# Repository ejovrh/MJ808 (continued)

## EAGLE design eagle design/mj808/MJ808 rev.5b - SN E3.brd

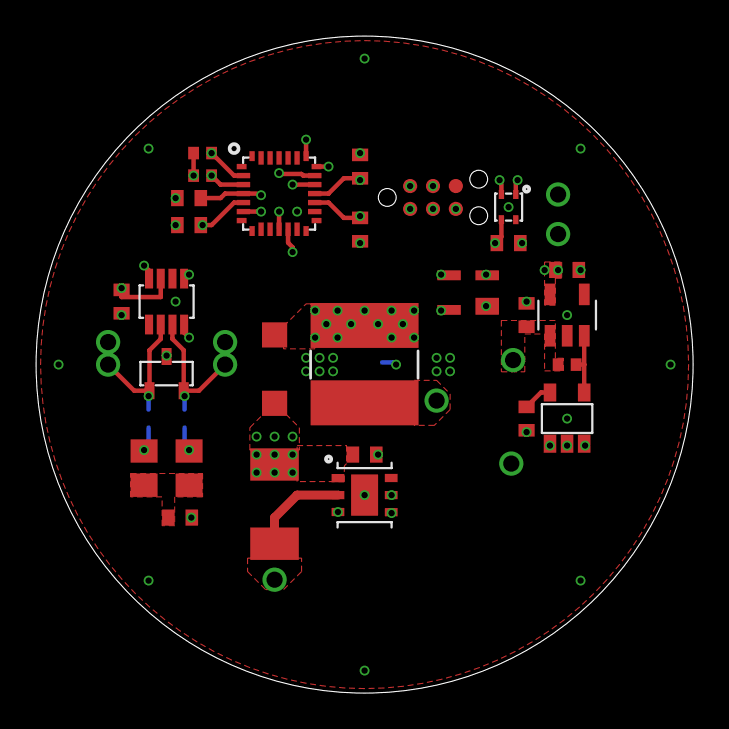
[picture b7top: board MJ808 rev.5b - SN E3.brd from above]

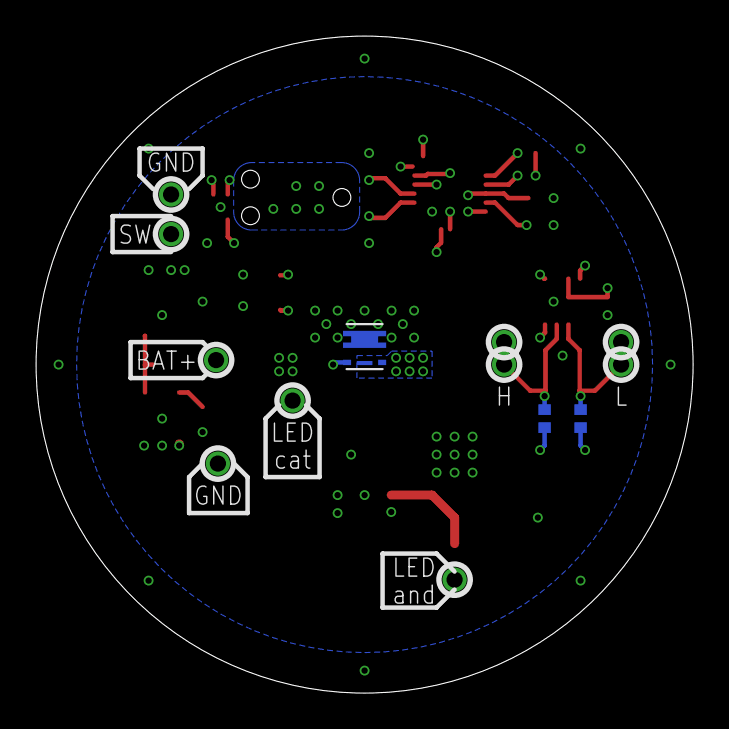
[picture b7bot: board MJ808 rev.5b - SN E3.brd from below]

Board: 4 copper layers, 36.5 x 36.5 mm, 41 parts (13 on the bottom side), 25 nets.

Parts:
C201, C202, C207, C304, C506: 1uF / 10V; C0402
C301, C305, C307, C405, C705: 0.1uF / 10V; C0402
C401: 47nF / 10V; C0402
D501: PMEG2010ER,115; SOD123
IC201: R3119N058A; SOT23-5
IC202: LDK320AM33R; SOT-23-5L
IC302: STM32F042G6U6; UFQFPN-28
IC401: TCAN334; SOT23-8
IC402: SZNUP2105LT1G; SOT-23-3
IC506: MAX16820; TDFN-6-EP
IC507: SQA470EEJ-T1_GE3; SC-70-6
IC602: MAX6816EUS+T; 4SOT143
IC701: SHT40-AD1F-R2; SMD
L501: VLS6045EX-150M-CA - 15uH; SRN6045
R201: 100k / 0.1W; R0402
R301, R302: 1k; R0402
R401, R402: 60R, 0.5W; R0805
R403, R404: 0; R0402
R504: 0.18R; R2010
SWD1: TC2030-NL
TP1: LiIon + Terminal; TH-0.9
TP2: LiIon - Terminal; TH-0.9
TP3, TP601, TP602: LED anode; TH-0.9
TP4: LED cathode; TH-0.9
TP5, TP7: CAN high; TH-0.9
TP6, TP8: CAN low; TH-0.9

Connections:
3V3: C207.2, C301.2, C304.2, C305.2, C405.1, C705.1, IC202.OUT, IC302.5_VDDA, IC302.17_VDD, IC302.18_VDDIO2, IC401.P$3, IC602.4_VCC, IC701.VDD, R301.2, R302.2, SWD1.1_TVCC
!STBY!: IC302.11_PA5, IC401.P$8
BAT+: C202.1, C506.1, D501.C, IC201.1_VDD, IC202.IN, IC506.IN, R201.1, R504.2, TP1.P$1
CAN_H: IC401.P$7, IC402.2, R403.2, TP5.P$1, TP7.P$1
CAN_INFRA:H: R402.2, R403.1
CAN_INFRA:L: R401.1, R404.1
CAN_INFRA:SPLIT: C401.1, R401.2, R402.1
CAN_L: IC401.P$6, IC402.1, R404.2, TP6.P$1, TP8.P$1
CAN_RX: IC302.19_PA9-[PA11], IC401.P$4
CAN_TX: IC302.20_PA10-[PA12], IC401.P$1
DIM_FRONT: IC302.12_PA6, IC506.DIM
FRONT_LED_DRIVER:DIM_FRONT_DRAIN: D501.A, IC507.1D, IC507.2D, IC507.5D, IC507.6D, IC507.D, L501.1
FRONT_LED_DRIVER:DIM_FRONT_GATE: IC506.DRV, IC507.3G
GND: C201.2, C202.2, C207.1, C301.1, C304.1, C305.1, C307.1, C401.2, C405.2, C506.2, C705.2, IC201.2_GND, IC201.3_GND, IC202.GND, IC302.16_VSS, IC401.P$2, IC402.3, IC506.GND, IC506.GND1, IC507.4S, IC507.S, IC602.1_GND, IC701.VSS, SWD1.5_GND, TP2.P$1, TP602.P$1
I2C_SCL: IC302.3_PF1, IC701.SCL, R302.1
I2C_SDA: IC302.2_PF0, IC701.SDA, R301.1
LED_AN: IC506.CSN, R504.1, TP3.P$1
LED_CA: L501.2, TP4.P$1
POWER_3V3:CD: C201.1, IC201.5_CD
POWER_3V3:EN: IC201.4_DOUT, IC202.EN, R201.2
PUSHBUTTON:SWITCH_IN: IC602.2_IN, TP601.P$1
SWITCH: IC302.6_PA0, IC602.3_OUT
SYS_NRST: C307.2, IC302.4_NRST, SWD1.3_T_NRST
SYS_SWCLK: IC302.22_PA14, SWD1.4_T_SWCLK
SYS_SWDIO: IC302.21_PA13, SWD1.2_T_SWDIO

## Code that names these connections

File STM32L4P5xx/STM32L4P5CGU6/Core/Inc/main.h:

/* USER CODE BEGIN Header */
/**
  ******************************************************************************
  * @file           : main.h
  * @brief          : Header for main.c file.
  *                   This file contains the common defines of the application.
  ******************************************************************************
  * @attention
  *
  * Copyright (c) 2025 STMicroelectronics.
  * All rights reserved.
  *
  * This software is licensed under terms that can be found in the LICENSE file
  * in the root directory of this software component.
  * If no LICENSE file comes with this software, it is provided AS-IS.
  *
  ******************************************************************************
  */
/* USER CODE END Header */

/* Define to prevent recursive inclusion -------------------------------------*/
#ifndef __MAIN_H
#define __MAIN_H

#ifdef __cplusplus
extern "C" {
#endif

/* Includes ------------------------------------------------------------------*/
#include "stm32l4xx_hal.h"

/* Private includes ----------------------------------------------------------*/
/* USER CODE BEGIN Includes */

/* USER CODE END Includes */

/* Exported types ------------------------------------------------------------*/
/* USER CODE BEGIN ET */

/* USER CODE END ET */

/* Exported constants --------------------------------------------------------*/
/* USER CODE BEGIN EC */

/* USER CODE END EC */

/* Exported macro ------------------------------------------------------------*/
/* USER CODE BEGIN EM */

/* USER CODE END EM */

/* Exported functions prototypes ---------------------------------------------*/
void Error_Handler(void);

/* USER CODE BEGIN EFP */

/* USER CODE END EFP */

/* Private defines -----------------------------------------------------------*/
#define TIMER_PRESCALER 799
#define TIMER2_PERIOD 0xFFFFFFFF
#define TIMER1_PERIOD 1249
#define TIMER1_PRESCALER 799
#define TIMER2_CH1_IC_FILTER 0xF
#define TIMER2_CH3_IC_FILTER 0xF
#define RN4678_SWButton_Pin GPIO_PIN_13
#define RN4678_SWButton_GPIO_Port GPIOC
#define RN4678_TransStat_Pin GPIO_PIN_14
#define RN4678_TransStat_GPIO_Port GPIOC
#define RN4678_ConnStat_Pin GPIO_PIN_15
#define RN4678_ConnStat_GPIO_Port GPIOC
#define HSE_IN_Pin GPIO_PIN_0
#define HSE_IN_GPIO_Port GPIOH
#define HSE_OUT_Pin GPIO_PIN_1
#define HSE_OUT_GPIO_Port GPIOH
#define ZeroCross_Pin GPIO_PIN_0
#define ZeroCross_GPIO_Port GPIOA
#define SDMMC_CMD_Pin GPIO_PIN_1
#define SDMMC_CMD_GPIO_Port GPIOA
#define DynamoCurrent_Pin GPIO_PIN_2
#define DynamoCurrent_GPIO_Port GPIOA
#define TCAN334_Standby_Pin GPIO_PIN_3
#define TCAN334_Standby_GPIO_Port GPIOA
#define AdjustableLoadDAC_Pin GPIO_PIN_4
#define AdjustableLoadDAC_GPIO_Port GPIOA
#define ADXL_INT1_Pin GPIO_PIN_5
#define ADXL_INT1_GPIO_Port GPIOA
#define QSPI_IO3_Pin GPIO_PIN_6
#define QSPI_IO3_GPIO_Port GPIOA
#define QSPI_IO2_Pin GPIO_PIN_7
#define QSPI_IO2_GPIO_Port GPIOA
#define QSPI_IO1_Pin GPIO_PIN_0
#define QSPI_IO1_GPIO_Port GPIOB
#define QSPI_IO0_Pin GPIO_PIN_1
#define QSPI_IO0_GPIO_Port GPIOB
#define RN4678_Reset_Pin GPIO_PIN_2
#define RN4678_Reset_GPIO_Port GPIOB
#define QSPI_SCK_Pin GPIO_PIN_10
#define QSPI_SCK_GPIO_Port GPIOB
#define QSPI_CS_Pin GPIO_PIN_11
#define QSPI_CS_GPIO_Port GPIOB
#define SDMMC_CLK_Pin GPIO_PIN_12
#define SDMMC_CLK_GPIO_Port GPIOB
#define SDMMC_CardDetect_Pin GPIO_PIN_13
#define SDMMC_CardDetect_GPIO_Port GPIOB
#define SDMMC_Data0_Pin GPIO_PIN_14
#define SDMMC_Data0_GPIO_Port GPIOB
#define SDMMC_Data1_Pin GPIO_PIN_15
#define SDMMC_Data1_GPIO_Port GPIOB
#define ApplicationLoadGate_Pin GPIO_PIN_8
#define ApplicationLoadGate_GPIO_Port GPIOA
#define RN4678_TX_Pin GPIO_PIN_9
#define RN4678_TX_GPIO_Port GPIOA
#define RN4678_RX_Pin GPIO_PIN_10
#define RN4678_RX_GPIO_Port GPIOA
#define RN4678_CTS_Pin GPIO_PIN_11
#define RN4678_CTS_GPIO_Port GPIOA
#define RN4678_RTS_Pin GPIO_PIN_12
#define RN4678_RTS_GPIO_Port GPIOA
#define AdjustableLoadGate_Pin GPIO_PIN_15
#define AdjustableLoadGate_GPIO_Port GPIOA
#define SDMMC_Data2_Pin GPIO_PIN_3
#define SDMMC_Data2_GPIO_Port GPIOB
#define SDMMC_Data3_Pin GPIO_PIN_4
#define SDMMC_Data3_GPIO_Port GPIOB
#define RN4678_Wakeup_Pin GPIO_PIN_5
#define RN4678_Wakeup_GPIO_Port GPIOB
#define I2C_SCL_Pin GPIO_PIN_6
#define I2C_SCL_GPIO_Port GPIOB
#define I2C_SDA_Pin GPIO_PIN_7
#define I2C_SDA_GPIO_Port GPIOB
#define LED_Reset_Pin GPIO_PIN_3
#define LED_Reset_GPIO_Port GPIOH
#define CAN_RX_Pin GPIO_PIN_8
#define CAN_RX_GPIO_Port GPIOB
#define CAN_TX_Pin GPIO_PIN_9
#define CAN_TX_GPIO_Port GPIOB

/* USER CODE BEGIN Private defines */

/* USER CODE END Private defines */

#ifdef __cplusplus
}
#endif

#endif /* __MAIN_H */

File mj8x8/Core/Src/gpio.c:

/* USER CODE BEGIN Header */
/**
  ******************************************************************************
  * @file    gpio.c
  * @brief   This file provides code for the configuration
  *          of all used GPIO pins.
  ******************************************************************************
  * @attention
  *
  * Copyright (c) 2022 STMicroelectronics.
  * All rights reserved.
  *
  * This software is licensed under terms that can be found in the LICENSE file
  * in the root directory of this software component.
  * If no LICENSE file comes with this software, it is provided AS-IS.
  *
  ******************************************************************************
  */
/* USER CODE END Header */

/* Includes ------------------------------------------------------------------*/
#include "gpio.h"

/* USER CODE BEGIN 0 */

/* USER CODE END 0 */

/*----------------------------------------------------------------------------*/
/* Configure GPIO                                                             */
/*----------------------------------------------------------------------------*/
/* USER CODE BEGIN 1 */

/* USER CODE END 1 */

/** Configure pins as
        * Analog
        * Input
        * Output
        * EVENT_OUT
        * EXTI
        * Free pins are configured automatically as Analog (this feature is enabled through
        * the Code Generation settings)
*/
void MX_GPIO_Init(void)
{

  GPIO_InitTypeDef GPIO_InitStruct = {0};

  /* GPIO Ports Clock Enable */
  __HAL_RCC_GPIOB_CLK_ENABLE();
  __HAL_RCC_GPIOF_CLK_ENABLE();
  __HAL_RCC_GPIOA_CLK_ENABLE();

  /*Configure GPIO pins : PB8 PB0 PB1 PB3
                           PB4 PB5 PB6 PB7 */
  GPIO_InitStruct.Pin = GPIO_PIN_8|GPIO_PIN_0|GPIO_PIN_1|GPIO_PIN_3
                          |GPIO_PIN_4|GPIO_PIN_5|GPIO_PIN_6|GPIO_PIN_7;
  GPIO_InitStruct.Mode = GPIO_MODE_ANALOG;
  GPIO_InitStruct.Pull = GPIO_NOPULL;
  HAL_GPIO_Init(GPIOB, &GPIO_InitStruct);

  /*Configure GPIO pins : PF0 PF1 */
  GPIO_InitStruct.Pin = GPIO_PIN_0|GPIO_PIN_1;
  GPIO_InitStruct.Mode = GPIO_MODE_ANALOG;
  GPIO_InitStruct.Pull = GPIO_NOPULL;
  HAL_GPIO_Init(GPIOF, &GPIO_InitStruct);

  /*Configure GPIO pins : PA0 PA1 PA2 PA3
                           PA4 PA5 PA6 PA7
                           PA15 */
  GPIO_InitStruct.Pin = GPIO_PIN_0|GPIO_PIN_1|GPIO_PIN_2|GPIO_PIN_3
                          |GPIO_PIN_4|GPIO_PIN_5|GPIO_PIN_6|GPIO_PIN_7
                          |GPIO_PIN_15;
  GPIO_InitStruct.Mode = GPIO_MODE_ANALOG;
  GPIO_InitStruct.Pull = GPIO_NOPULL;
  HAL_GPIO_Init(GPIOA, &GPIO_InitStruct);

}

/* USER CODE BEGIN 2 */

/* USER CODE END 2 */

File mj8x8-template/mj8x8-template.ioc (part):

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Mcu.Name=STM32F042G(4-6)Ux
Mcu.Package=UFQFPN28
Mcu.UserName=STM32F042G6Ux
PA11.Mode=CAN_Activate
PA11.Signal=CAN_RX
PA12.Mode=CAN_Activate
PA12.Signal=CAN_TX
PA13.Mode=Serial_Wire
PA13.Signal=SYS_SWDIO
PA14.Mode=Serial_Wire
PA14.Signal=SYS_SWCLK
board=custom

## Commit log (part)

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2024-11-13 created a gateway board for uart <-> CAN communication
2024-11-13 - added code, board & schematics for mj000 - the future logic unit
2024-11-13 - code adjustment to match base
2024-11-13 small corrections after rebase/merge
2024-11-13 some forgotten work from half a year ago
2024-11-13 ...initial commit. lets see how far this will go.
2024-11-13 small changes in terms of whitespace and try_ctor()
2024-11-13 added bottom place marker for hall sensor
2024-11-13 added e14 board top&bottom picture with annotations
2024-11-13 added IC symbols and footprints to e14 sch & brd
2024-11-13 added e14 blank - mostly for board outline for easy copy'n'paste into POC
2024-11-13 moved e14 reverse engineering to seperate branch, moved mj514 POC into POC branch
2024-11-13 added mj512 board outline - a slightly changed outline in respect to the original e14
2024-11-13 corrected mj8x8_commands.h and saleae's HLA code for mj514
2024-11-13 - added AS5601 - Programmable Contactless Encoder and MB85RC - FeRAM, I2C libraries and added them to schematic - defined GPIOs for above ICs
2024-11-13 in mj514.c/.h & as5601.c/.h - wrote untested timer3 / DMA init code for DMA-based rotary mode so that A & B output of as5601 can be interpreted
    in sch & brd:
    - renamed as5601 A & B lines to match GPIOInit() in mj514.c
2024-11-13 in brd & sch: - corrected/renamed rotary A & B nets - changed Rpullup for I3C bus from 10k to 4k7
2024-11-13 - implemented crude timer2 in encoder mode
2024-11-13 in mj514.c and as5601.c: - daisy chained start/stop of timer2 to timer3
2024-11-13 work on a I2C skeleton driver applied skeleton to I2C users
    heavily untested code !
2024-11-13 in mj514.c/.h & as5601.c: - moved timer2 (quad channel) to timer16 (single channel) so that timer2's two channels can be used for motor control PWM
2024-11-13 in mj514.c/.h: #define-d required constants - in _GPIOInit(): defined GPIOs for peripheral device control (motor controller, FeRAM) - in _TimerInit(): defined required timers - implemented timer star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
    in motor.c:
    - implemented rough start and stop functions for peripheral sleep/wakeup
    added mj514_adc.c:
    - copied adc code from mj828 and adapted it to mj514's needs
2024-11-13 mj514 rev.1 PCB first rough layout is complete
2024-11-13 in AutoDevice.py: - fixed hex "c" to 12 translation in dictionary
2024-11-13 board rev 1a: corrected rotary encoder sensor position
2024-11-13 in try.c: - correction of try_ctor() for mj514
2024-11-15 added mj514 datasheets
2024-11-16 - annotated stm32 pins/ports for I2C and rotary encoder channels A and B
2024-11-17 in schematic: corrected I2C GPIOs
2024-11-18 in i2c.c/.h: - added portb peripheral clock start - added I2C handler as public object - corrected low-level I2C peripheral init code - removed code from original read/write functions; they are now s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
    in device drivers which use I2C (FeRAM, rotary encoder):
    - copied read/write code developed in different project into files, adapted other related code
    - removed calls for old generic I2C write/read
    in mj514.c/.h:
    - corrected timer init, start and stop functions - they all still need to be verified
    - removed FeRAM WP GPIO
2024-11-19 timer2 PWM is tested and works
2024-11-19 repairs of code tree (deletions in mj514 branch) before merge into master
2024-11-19 added Rohloff E14 board outline - reverse engineered based on the original E14 PCB to fit into E14 housing
2024-11-21 in i2c.c/.h: - wrote read and write functions that are meant to be consolidated: client devices are meant to call I2C write/read functions in their own read/write calls, i.e. calling core I2C read./w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
    in as5601.c/.h and mb85rc.c/.h:
    - adapted for consolidated I2C read/write functions
    - removed few FIXMEs
    created some testing for FeRAM and motor controller
    in all mj-devices:
    -moved "application part" of code init (e.g. in mj514.c) so that init via constructors starts afte
2024-12-23 in mj514.c/.h: - activated application ctor where it ought to be and removed the temporary one - reorganized code so that adc init can exit with calling the adc stop function, thereby leaving the per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
2024-12-23 - updated mj8x8 template project after cubeide update to v.1.17
2024-12-23 - added device-specific dwg's into repository
2024-12-23 - cubeide upgrade to v.1.17
2024-12-23 mj515 work: - added codebase for mj515 - added datasheers for mj515 - added mj515 - the electronic Drehgriff - hardware design files
2024-12-23 mj515 dwg work: - created cross section paperspace for all relevant macroscopic objects
    grip body.dwg:
    - updated cable stops
    mj515/2 - grip inner.dwg & mj515/3 - grip proper.dwg:
    - extended the rotation pattern to go over a 16 position range over 360 degrees (instead of 14 positions over 273 degrees)
    this allows for incremental operation or 14 position operation
    mj515/4 - encoder foil.dwg:
2024-12-23 in all dwg's: - moved reference lines to its own layer
    in mj808/SuperNova E3 base.dwg:
    - corrected screw hole diameter
2024-12-23 in mj808 & mj818 design: - added 2nd TH via for CAN H & L connection
2024-12-26 cleanup before rebase
2024-12-26 mj838 project: - added GnZC files
2025-01-03 in GnZC - POC.brd/sch: - updated conceptual overview to include 3V3 LDO - moved LDO reverse protection diode into 3V3 sheet - changed 3V3 power symbol
2025-01-08 general board-wide effort: - replaced pinhead with 0.9mm TH - added 2nd CAN H & L solder contact - unified sch nets and drawings
    in mj8x8 foo:
    - developed rev.1b mj-foo device with voltage detector and CAN TVS protection
    in mj808 design:
    - updated front led shunt resistor to 0.18 Ohm
2025-01-22 MJ818 SuperNova Mini2: - added position key into PCB and spacers; updated gerber, dwg and stl
    mj513 - grip:
    - corrected bushing dimensions
    in mj8x8-foo:
    - minor corrections
    general board-wide effort:
    - replaced pinhead with 0.9mm TH
2025-01-23 minor corrections on BOM
2025-01-23 - created MJfoo device BOM
2025-01-26 MJ514 - rev.1 - POC: - removed humidity sensor
2025-01-27 - seperated MJ8x8 clone - rev.5 - TCAN334 - poc.brd(generic) BOMs from device specific
2025-01-27 in gear.c: - implemented logic to store a cumulative pulse count (as measured by the as5601) - implemented logic to store a cumulative gears shifted count
2025-02-11 ---------------------------- in mj514.c/.h: - worked around the EXTI3 problem when the motor controller is enabled - added PA5 - 12V0 regulator shutdown pin (preparation for HW rev. 1a) - added one m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
    in i2c.c/.h:
    - added switch for DMA vs. IT calls
    - added a define which controls HAL_I2C_IsDeviceReady()
    in motor.c/.h:
    - added basic angle & current statistics
    - added #if USE_AS5601_PULSE to deactivate rotary encoder A/B channel code
2025-02-14 --- HW rev.1 ---
    in mj838.c/.h:
    - removed solid-state relay control GPIO initialization in _GPIOInit()
    - added (float) typecast to fix compiler warnings
    in autocharge.c:
    - added typecast for __AutoCharge.__SW_C* to avoid compiler warnings
    - commented out solid-state relay control GPIO initialization in autocharge_ctor()
2025-02-14 . in mj838.c/.h: - removed solid-state relay control GPIO initialization in _GPIOInit() - added (float) typecast to fix compiler warnings
    in autocharge.c:
    - added typecast for __AutoCharge.__SW_C* to avoid compiler warnings
    - commented out solid-state relay control GPIO initialization in autocharge_ctor()
    in autodrive.c
    - added (float) typecast to fix compiler warnings
    in mj838_zerocross.c:
2025-02-14 corrected BOM
2025-03-23 HW rev.1 validation & various bug fixes
    in mj8x8.c:
    - if I2C is used, HAL_Delay() is needed: created a preprocessor #if to address that
    for mj808:
    - added code which turns off util. LED blinking for supernova hardware
    in mj838.c/.h:
    - renamed debug GPIOs from 0 and 1 to yellow and blue (according to the test pad color)
2025-03-26 HW rev.1a finished
    in mj838.brd/.sch:
    - added adjustable current sink by means of a N-Fet gate driven by an opamp, in turn controlled by a voltage supplied by a a I2C controlled DAC connected to the opamp's inverting input.
    - moved almost all elements to top layer. exceptions are for now SSRs.
    - added DAC121C081 - 12bit I2C DAC datasheet and eagle lib
    - added TName indicators for easier probing of SSD relay contact points between TLC59208F and SSR LED cathode
    - reconfigured 12R artifical load to permanently have a 12R SMD resistor on board
2025-04-04 in board design: - added current sense resistor calculation - in 12V0 regulator added slow start RC lowpass filter, as per DS. p. 6 - moved 12V_SHDN to PA5
    in motor.c/.h:
    - code tweaks for angle statistics
    - added #if USE_AS5601_PULSE across the code to deactivate not needed code
    - in timer16 ISR: added _EndTravelTime and coded setting this variable with the elapsed milliseconds once the travel end is reached
    - in timer16 ISR: added code which allows timer16 to continue to run after end travel is reached
    - in _StartMotorController() & _StopMotorController() added timer16 interrupt priority change (suspect was some race condition or priority collision)
2025-04-06 in mj838_zerocross.c: - fixed bug where ZC would start immediately after being stopped, was due to not properly clearing the EXTI0 flag
2025-04-11 in pac1952.c/.h: - removed Vbus, Vsense, Vpower getter functions - imnplemented Vbus. Vsense and manual Vpower calculation
    in mj838_zerocross.c:
    - in _Do() called Device->AutoDrive->AutoDriveOn() once zerocross delta (i.e. wheel rotation -> movement) is detected
    - modified timer2 ARR to 1 second on detection of lack of zerocross delta (i.e. no wheel rotation -> no movement)
    - fixed bug where ZC would start immediately after being stopped, was due to not properly clearing the EXTI0 flag
    in mj838.c:
    - in mj838_ctor() corrected call which clears pending interrupts
2025-04-18 /// start of MJ808 rev.5b - SN E3 /// - added CAN protection diode - added power supervisor - replaced CAN solder bridges with 0402 resistors - adapted silkscreen stuff a bit - renamed files, updated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
2025-05-27 . - added dac121c081 object files - an abstraction of the I2C DAC121C081 DAC IC
2025-05-27 . in sch: added I2C address of DAC to adjustable load sheet
    in dac121c081.c/.h:
    - adapted read/write functions to one-register reads/writes
2025-05-27 . in autocharge.c/.h: - renamed classic load switch to application load switch since on HW rev.1b there will be a dedicated application load in parallel to a 12R adjustable load
2025-05-27 . in mj838.c/.h: - added timer14 - 1ms for PAC1952 power measurements while charger is on - since code change came too early, included #define for rev.1 GPIO layout in rev.1a code branch
    in autocharge.c:
    - in _SetChargerState() added code which starts/stops timer14
2025-05-27 . in autocharge.c/.h: - surrounded application load functions/objects with #if USE_APPLICATION_LOAD
    in mj838_zerocross.c:
    - surrounded application load functions/objects with #if USE_APPLICATION_LOAD
    in try.c:
    - surrounded application load functions/objects with #if USE_APPLICATION_LOAD
2025-05-27 . in mj838.c/.h: - reduced timer14 to 10ms
2025-05-27 ////// start of MJ838 HW rev.1b //////
    in spice simulation:
    - in ZeroCross detection circuit, replaced OpAmp comparator with dedicated comparator, added OptoCoupler
    - added experimental 2xNMos + OptoCoupler circuit for Zerocross detection
    in brd & sch:
    - added a bit of TVS/ESD protection for SWD, 3V3 bus
    - in zerocross sheet, added 4N25 optocoupler to comparator output
2025-05-27 /// mj838 rev.1b sent to fab ///
2025-08-25 in sch: - changed I2C pullup resistors to 1k
2025-11-16 - minor code corrections for rev. 5b compile
